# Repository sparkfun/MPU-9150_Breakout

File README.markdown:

These are the most up to date hardware and firmware files for the [MPU-9150 Breakout](https://www.sparkfun.com/products/11486) at SparkFun Electronics.

The MPU-9150 is an accelerometer, gyro, and magnetometer all in a single package with an I2C interface. 

The hardware directory contains the Eagle design files and the firmware directory contains an Arduino library with an example that send raw sensor data out of the serial port. 

Hardware License
====
[Creative Commons Attribution-ShareAlike](http://creativecommons.org/licenses/by-sa/3.0/)

Author: Aaron Weiss @ SparkFun Electonics

Firmware License
====
From the original author [Jeff Rowberg](https://github.com/jrowberg/i2cdevlib), jeff@rowberg.net 
Modified by Aaron Weiss, aaron@sparkfun.com

The Arduino library code is placed under the MIT license:

Permission is hereby granted, free of charge, to any person obtaining a copy
of this software and associated documentation files (the "Software"), to deal
in the Software without restriction, including without limitation the rights
to use, copy, modify, merge, publish, distribute, sublicense, and/or sell
copies of the Software, and to permit persons to whom the Software is
furnished to do so, subject to the following conditions:

The above copyright notice and this permission notice shall be included in
all copies or substantial portions of the Software.

THE SOFTWARE IS PROVIDED "AS IS", WITHOUT WARRANTY OF ANY KIND, EXPRESS OR
IMPLIED, INCLUDING BUT NOT LIMITED TO THE WARRANTIES OF MERCHANTABILITY,
FITNESS FOR A PARTICULAR PURPOSE AND NONINFRINGEMENT. IN NO EVENT SHALL THE
AUTHORS OR COPYRIGHT HOLDERS BE LIABLE FOR ANY CLAIM, DAMAGES OR OTHER
LIABILITY, WHETHER IN AN ACTION OF CONTRACT, TORT OR OTHERWISE, ARISING FROM,
OUT OF OR IN CONNECTION WITH THE SOFTWARE OR THE USE OR OTHER DEALINGS IN
THE SOFTWARE.

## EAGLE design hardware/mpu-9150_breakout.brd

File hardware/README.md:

Eagle files for the MPU-9150 Breakout. See the commit history for the hardware version numbers.

License: Creative Commons Attribution-ShareAlike 3.0 (CC BY-SA 3.0)
http://creativecommons.org/licenses/by-sa/3.0/

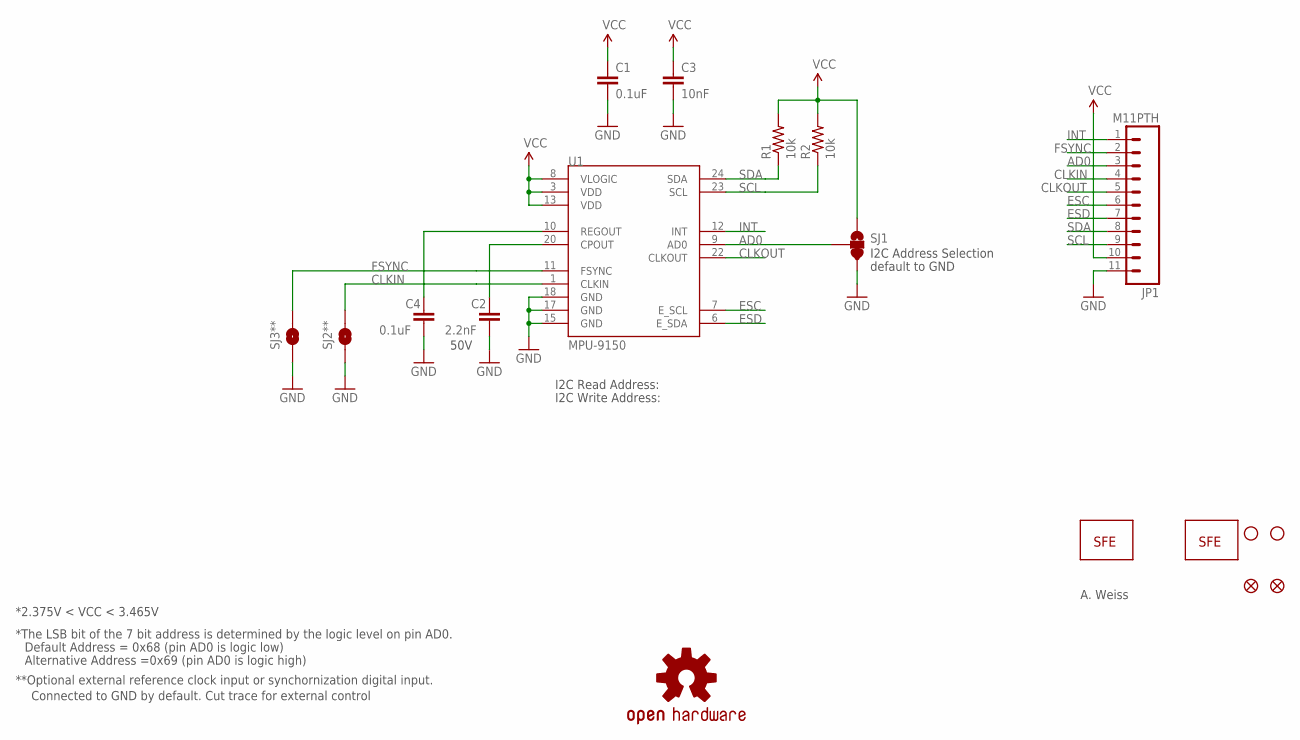
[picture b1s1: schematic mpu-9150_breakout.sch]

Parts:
C1, C4: 0.1uF; 0402-CAP
C2: 2.2nF; 0402-CAP
C3: 10nF; 0402-CAP
JP1: M11PTH; 1X11
JP2, JP3: STAND-OFF
JP4: LOGO-SFENW2; SFE-NEW-WEB
JP6: LOGO-SFESK; SFE-LOGO-FLAME
JP7, JP8: FIDUCIALUFIDUCIAL; MICRO-FIDUCIAL
R1, R2: 10k; 0402-RES
SJ1: SOLDERJUMPER_2WAYPASTE2&3; SJ_3_PASTE2&3
SJ2**, SJ3**: SOLDERJUMPERTRACE; SJ_2S-TRACE
U1: MPU-9150; QFN-24-NP
U$1: OSHW-LOGOS; OSHW-LOGO-S

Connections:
AD0: JP1.3, SJ1.2, U1.9 (AD0)
CLKIN: JP1.4, SJ2**.2, U1.1 (CLKIN)
CLKOUT: JP1.5, U1.22 (CLKOUT)
ESC: JP1.6, U1.7 (E_SCL)
ESD: JP1.7, U1.6 (E_SDA)
FSYNC: JP1.2, SJ3**.2, U1.11 (FSYNC)
GND: C1.2, C2.2, C3.2, C4.2, JP1.11, SJ1.3, SJ2**.1, SJ3**.1, U1.15 (GND), U1.17 (GND), U1.18 (GND)
INT: JP1.1, U1.12 (INT)
unnamed: C2.1, U1.20 (CPOUT)
unnamed: C4.1, U1.10 (REGOUT)
SCL: JP1.8, R2.1, U1.23 (SCL)
SDA: JP1.9, R1.1, U1.24 (SDA)
VCC: C1.1, C3.1, JP1.10, R1.2, R2.2, SJ1.1, U1.3 (VDD), U1.8 (VLOGIC), U1.13 (VDD)

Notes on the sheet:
50V
I2C Address Selection
**Optional external reference clock input or synchornization digital input.
Connected to GND by default. Cut trace for external control
Default Address = 0x68 (pin AD0 is logic low)
Alternative Address =0x69 (pin AD0 is logic high)
*The LSB bit of the 7 bit address is determined by the logic level on pin AD0.
default to GND
A. Weiss
*2.375V < VCC < 3.465V
I2C Read Address:
I2C Write Address:

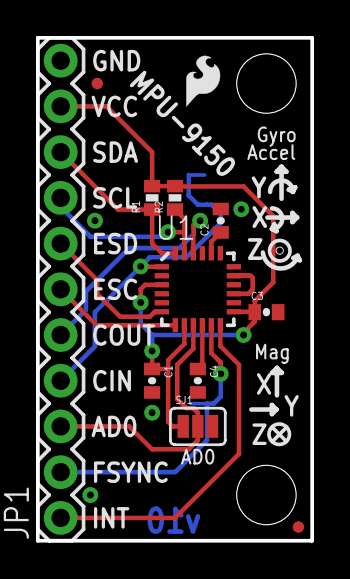
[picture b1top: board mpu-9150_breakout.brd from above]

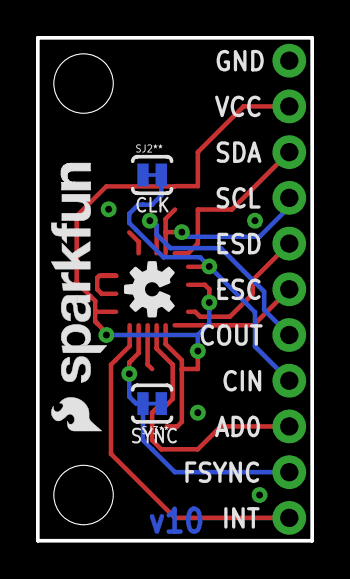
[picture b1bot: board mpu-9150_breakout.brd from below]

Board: 2 copper layers, 15.2 x 27.9 mm, 19 parts (5 on the bottom side), 13 nets.

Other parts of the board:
JP5: LOGO-SFESK; SFE-LOGO-FLAME

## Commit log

2013-01-04 first
2013-01-04 editied schematic
    removed some old txt
2013-01-04 added markdown readmes
2013-01-04 cleanup
    added gitignore
2013-01-04 v10 hardware
2013-01-07 Corrected register value
2013-01-23 fixed mag output
    mag output was actually accel output. needed to enable bypass mode on
    the 9150, then enable the mag
2013-03-08 standardizing README via organization, linking to licenses, etc.
2013-12-20 Fixing SDA/SCL labels on schematic
2014-03-09 correct bug in getMotion9
2014-04-10 Create MPU9150_AHRS
    Sketch to read accelerometer, gyro, and magnetometer data from MPU9150 sensor and fuse the sensor input to a quaternion representation using Madgwick's or Mahony's open-source 9 DoF sensor fusion fil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
    Sketch runs on a 3.3 8 MHz Pro Mini Arduino microcontroller with filter update rates of between 125 and 165 Hz.
2014-04-10 Rename MPU9150_AHRS to MPU9150_AHRS.ino
2014-04-10 Update MPU6050_9Axis_MotionApps41.h
    Added read functions for gyro and magnetometer
2014-04-10 Update MPU6050.h
    Added read function for gyro and magnetometer
2014-04-10 Update MPU6050.cpp
    Added read functions for gyro and magnetometer
2015-02-23 Update MPU6050.cpp
    MPU9150 and MPU6050 RA_WHO_AM_I is read only
2015-03-07 Changed from using prog_uchar types so the motion apps files compile in Arduino 1.6.0
2015-07-10 Removed function that tried to write to a read-only register
2015-07-10 Corrected mask on DATA_RDY_INT
2016-02-04 Typos?
    The header description had the the file's name wrong, and the note about the maximum voltage referred to another IMU (LSM9DS0).
2016-03-26 Fix OUTPUT_READABLE_WORLDACCEL
2025-06-24 Update README.md
    Update Photo Link
2025-06-24 Update README.md
    Update datasheet link.
2025-06-27 Update MPU9150_AHRS.ino
    Updating links

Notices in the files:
parts and their libraries:
SparkFun-Sensors: Licensing: CC v3.0 Share-Alike You are welcome to use this library for commercial purposes.
SparkFun-Aesthetics: Released under the Creative Commons
